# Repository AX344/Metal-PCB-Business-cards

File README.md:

# Metal-PCB-Business-cards
This repository contains the KiCad files for metal PCB business cards.

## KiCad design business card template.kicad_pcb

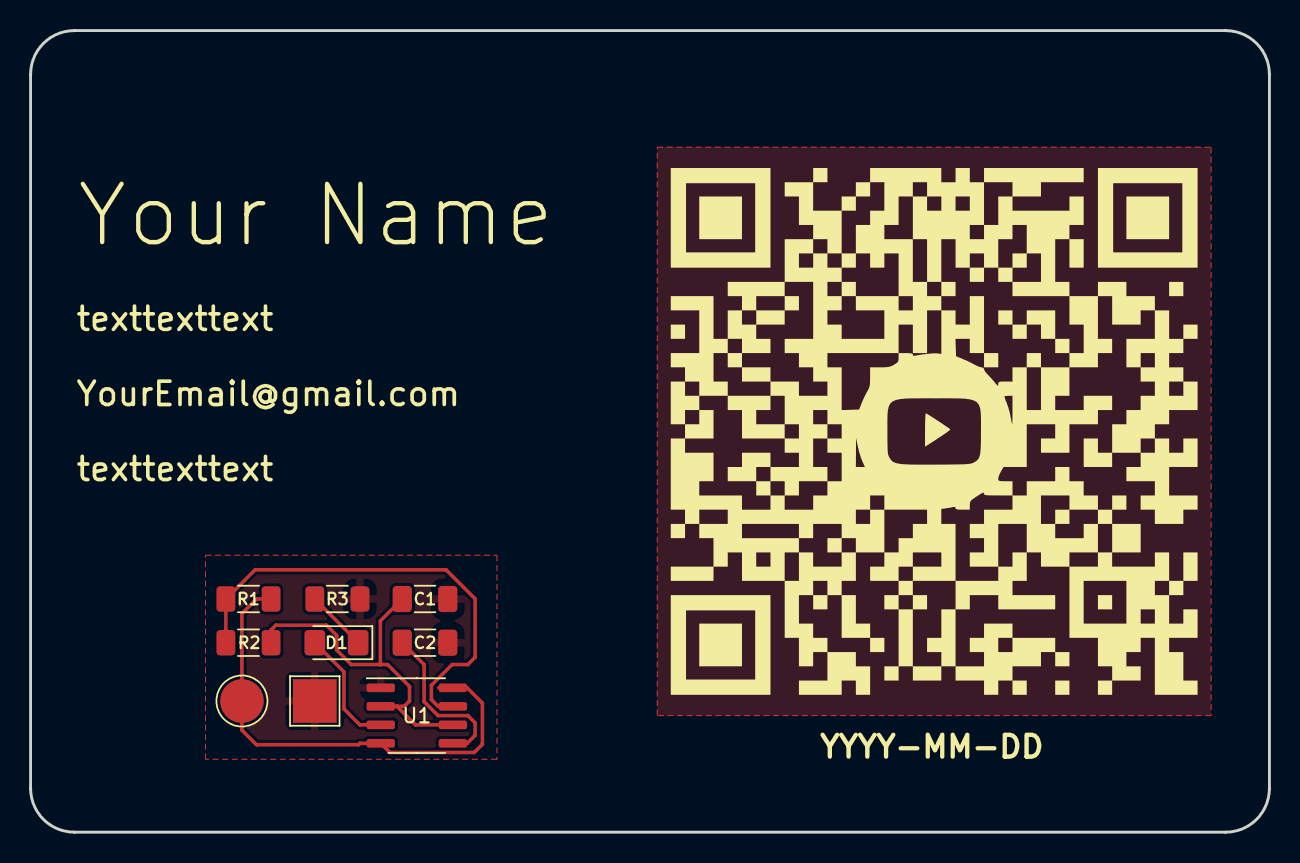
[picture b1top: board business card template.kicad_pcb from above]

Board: 2 copper layers, 85.0 x 55.0 mm, 10 parts (0 on the bottom side), 7 nets.

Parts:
C1, C2: C; C_1206_3216Metric_Pad1.33x1.80mm_HandSolder
D1: LED; LED_1206_3216Metric_Pad1.42x1.75mm_HandSolder
G1: LOGO
R1, R2, R3: R; R_1206_3216Metric_Pad1.30x1.75mm_HandSolder
TP1: TestPoint; TestPoint_Pad_D3.0mm
TP2: TestPoint; TestPoint_Pad_3.0x3.0mm
U1: NE555D; SOIC-8_3.9x4.9mm_P1.27mm

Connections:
Earth: C1.2, C2.2, R3.2, TP2.1, U1.1 (GND)
unnamed: D1.2 (A), U1.3 (Q)
unnamed: D1.1 (K), R3.1
unnamed: C2.1, U1.5 (CV)
unnamed: R1.2, R2.1, U1.7 (DIS)
unnamed: R1.1, TP1.1, U1.4 (R), U1.8 (VCC)
unnamed: C1.1, R2.2, U1.2 (TR), U1.6 (THR)

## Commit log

2024-12-13 added KiCad files
